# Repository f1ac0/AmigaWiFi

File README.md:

# AmigaWiFi
Three different RS232 WiFi boards with ESP8266 to connect the Amiga to the world with Zimodem or esp\_slip\_router firmwares.

With Zimodem (https://github.com/bozimmerman/Zimodem) by Bo Zimmerman, this board can connect to telnet/BBS/xyzmodem/kermit services over IP on your local network or Internet.

With esp\_slip\_router (https://github.com/martin-ger/esp\_slip\_router) by Martin Ger, this board is a SLIP router to connect your Amiga to Internet.

The boards :
- AmigaWiFi3232_external : plugs into the DB25 serial port. Provides TX/RX/RTS/CTS for communication and hardware flow control. Needs external 5V supply through micro or mini-USB.
- AmigaWiFi3232_internal : connects internally. Provides TX/RX/RTS/CTS for communication and hardware flow control.
- AmigaWifi3237 : plugs into the DB25 serial port. Provides TX/RX/RTS/CTS/DTR/DSR/DCD/RI for communication, hardware flow control, carrier detect, ring. Needs external 5V supply through micro or mini-USB. Also has LED and display header that are not implemented at the moment.

Please note that the serial port on Amiga suffers some limitations. It is dependent on CPU speed : do not expect stable transfer at more than 33600 bauds with a 7MHz 68000, even with new8n1/baudbandit serial drivers. It is also dependent on screen bitplanes so you may need to set a 4 or even 2 colours mode before transfer.

# Disclaimer
This is a hobbyist project, it comes with no warranty and no support. Also remember that the Amiga machines are about 30 years old and may fail because of such hardware expansions.

This board is not connected to the firmware authors, please don't bother them with issues you might have because of it.

I publish this work using the CC-BY-NC-SA license.

If you find it useful and want to reward me : I am always looking for Amiga/Amstrad CPC hardware to repair and hack, please contact me.

# Making it
Some components are SMD. You need to know what you are doing.

Check for shorts at least between 5V, 3.3V, and GND traces before applying power !

The programming port does not need to be soldered since it needs to be programmed just once : you can just hold it in place during the few seconds required for programming.

The ESP8266 has to be programmed with a firmware. 3232 boards need to be programmed through a RS232 serial port on your PC so you need to physically connect it to the DB9 plug (commercial or homemade adapter). 3237 board can be programmed through its RS232 DB25 or through a TTL header depending on how you build it : check the schematic. In all cases you need to connect TX of the PC to RX of the board and vice-versa.

If you use the internal version of the board, disconnect any external device from the serial port. They cannot be used at the same time.

# Using it with Zimodem
Check the Zimodem project page on how to build it with the Arduino framework.

It is required to set the pinouts before building :
```
# define DEFAULT_PIN_DSR 5  //To computer DSR
# define DEFAULT_PIN_DTR 4  //To computer DTR
# define DEFAULT_PIN_RI 2 //To computer RI
# define DEFAULT_PIN_RTS 15 //To computer CTS (warning switched)
# define DEFAULT_PIN_CTS 13 //To computer RTS (warning switched)
# define PIN_EN 12
# define PIN_SHDN 14
```

In addition for 3237 version, enable the serial converter at beginning of setup :
```
void setup()
{
#ifdef PIN_EN //Enable 3237
  pinMode(PIN_EN, OUTPUT);
  digitalWrite(PIN_EN, LOW);
#endif
#ifdef PIN_SHDN //unSHDN 3237
  pinMode(PIN_SHDN, OUTPUT);
  digitalWrite(PIN_SHDN, HIGH);
#endif
```

Setup on the Amiga :
- install some terminal software like Term_4.8
- Setup serial device with appropriate baud rate, high speed mode (8N1), appropriate flow control, NO XON/XOFF. Disable local Echo.
- Setup transfer directories, then activate zmodem auto download
- Setup Zimodem:
```
ATI
ATB38400
ATW
ATW"ssid,pwd"
AT&W
```

To connect to a telnet/bbs service :
```
ATDT"towel.blinkenlights.nl:23"
```

To transfer a file from a PC on the LAN using sz :
- On the PC : `sz -b --tcp-server Files/to/transfer Another/file/to/transfer`
- Then on the Amiga connect to your PC IP and port given by sz : `ATD"192.168.1.2:32999"`
Transfer the file to the PC :
- On the Amiga : `ATA1234`
- On the PC : `sz -b --tcp-client 192.168.1.5`

If there are too many errors and retries :
- Lower the number of colours of the terminal app or Workbench.
- Increase buffers on Amiga.
- Activate hardware flow control both on Zimodem `ATF0` and Amiga (not sure if this is meaningful though). Use `ATF4` to disable it.
- Lower bitrate both on Zimodem `ATB19200` and Amiga (not too much otherwise sz will timeout during transfer).

# Using it with esp_slip_router
Check the esp\_slip\_router page on how to build the firmware.

By default the project does not use hardware flow control. You can choose to activate it before building, which will let you use the baudbandit serial driver on the Amiga. However beware that slattach during the PC test and setup procedure will not work anymore. To enable it, make these changes in include/driver/uart.h :
```
UART_HW_RTS 1
UART_HW_CTS 1
```

To setup the Amiga side I followed the guide : https://blog.nootch.net/post/amiga-bbs-online-2019/. With few additions : enable the "ignore DSR" feature, disable "Carrier detect" and use the "New8N1" serial driver. It works on my A600 with 68020 but Genesis does not work on my A500 with 68010 (not only the license file but also starting the app).

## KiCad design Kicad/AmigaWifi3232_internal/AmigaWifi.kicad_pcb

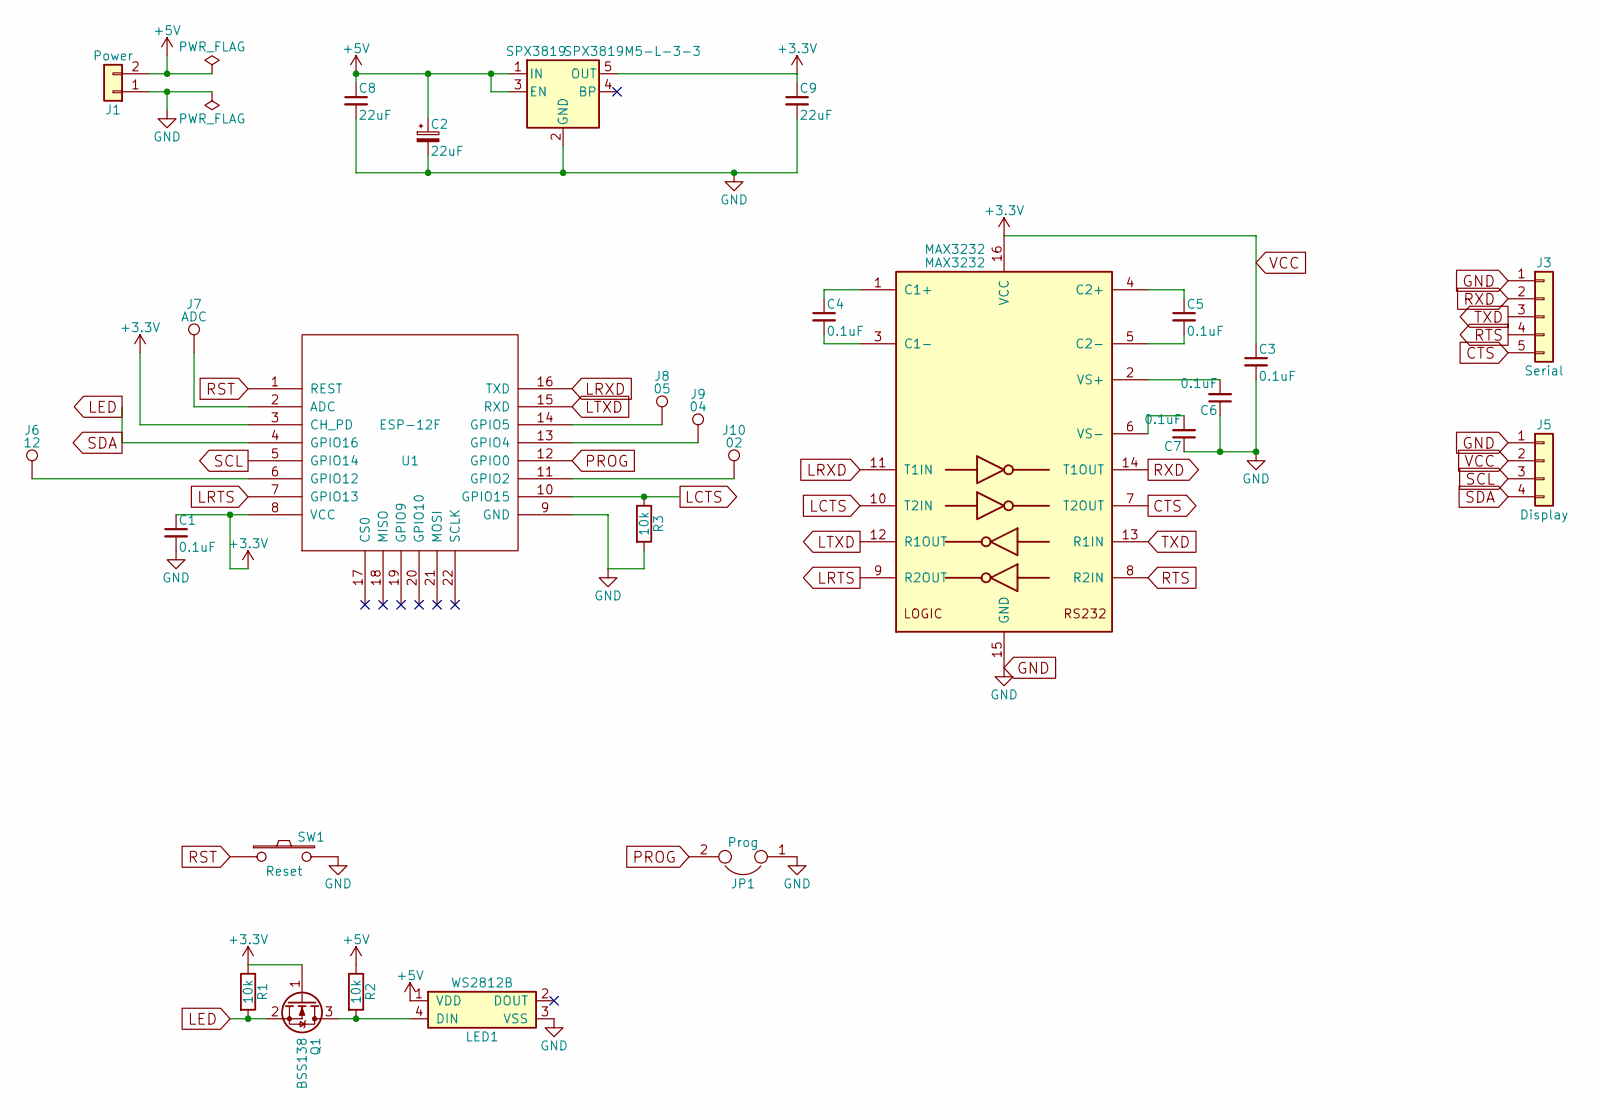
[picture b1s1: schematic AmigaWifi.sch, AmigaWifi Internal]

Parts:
C1, C3, C4, C5, C6, C7: 0.1uF; C_0805_HandSoldering
C2: 22uF; CP_Radial_D5.0mm_P2.50mm
C8, C9: 22uF; C_0805_HandSoldering
J1: Power; Pin_Header_Straight_1x02_Pitch2.54mm
J3: Serial; Pin_Header_Straight_1x05_Pitch2.54mm
J5: Display; Pin_Header_Straight_1x04_Pitch2.54mm
J6: 12; Measurement_Point_Round-SMD-Pad_Small
J7: ADC; Measurement_Point_Round-SMD-Pad_Small
J8: 05; Measurement_Point_Round-SMD-Pad_Small
J9: 04; Measurement_Point_Round-SMD-Pad_Small
J10: 02; Measurement_Point_Round-SMD-Pad_Small
JP1: Prog; Pin_Header_Straight_1x02_Pitch2.54mm
LED1: WS2812B; LED_WS2812B-PLCC4
MAX3232: MAX3232; SOIC-16_3.9x9.9mm_Pitch1.27mm
Q1: BSS138; SOT-23_Handsoldering
R1, R2, R3: 10k; R_0805_HandSoldering
SPX3819: SPX3819M5-L-3-3; SOT-23-5_HandSoldering
SW1: Reset; SW_SPST_FSMSM
U1: ESP-12F; ESP-12E_SMD

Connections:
+5V: C2.1, C8.1, J1.2, LED1.1 (VDD), R2.1, SPX3819.1 (IN), SPX3819.3 (EN)
CTS: J3.5, MAX3232.7 (T2OUT)
GND: C1.2, C2.2, C3.2, C6.1, C7.1, C8.2, C9.2, J1.1, J3.1, J5.1, JP1.1, LED1.3 (VSS), MAX3232.15 (GND), R3.2, SPX3819.2 (GND), SW1.2, U1.9 (GND)
LCTS: MAX3232.10 (T2IN), R3.1, U1.10 (GPIO15)
LED: J5.4, Q1.2 (S), R1.2, U1.4 (GPIO16)
LRTS: MAX3232.9 (R2OUT), U1.7 (GPIO13)
LRXD: MAX3232.11 (T1IN), U1.16 (TXD)
LTXD: MAX3232.12 (R1OUT), U1.15 (RXD)
unnamed: C4.1, MAX3232.1 (C1+)
unnamed: C4.2, MAX3232.3 (C1-)
unnamed: C5.1, MAX3232.4 (C2+)
unnamed: C5.2, MAX3232.5 (C2-)
unnamed: C6.2, MAX3232.2 (VS+)
unnamed: C7.2, MAX3232.6 (VS-)
unnamed: J6.1, U1.6 (GPIO12)
unnamed: J7.1, U1.2 (ADC)
unnamed: J8.1, U1.14 (GPIO5)
unnamed: J9.1, U1.13 (GPIO4)
unnamed: J10.1, U1.11 (GPIO2)
unnamed: LED1.4 (DIN), Q1.3 (D), R2.2
PROG: JP1.2, U1.12 (GPIO0)
RST: SW1.1, U1.1 (REST)
RTS: J3.4, MAX3232.8 (R2IN)
RXD: J3.2, MAX3232.14 (T1OUT)
SCL: J5.3, U1.5 (GPIO14)
TXD: J3.3, MAX3232.13 (R1IN)
VCC: C1.1, C3.1, C9.1, J5.2, MAX3232.16 (VCC), Q1.1 (G), R1.1, SPX3819.5 (OUT), U1.3 (CH_PD), U1.8 (VCC)

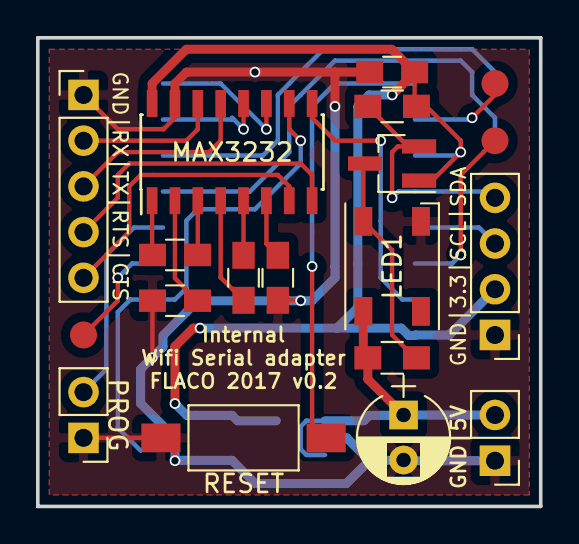
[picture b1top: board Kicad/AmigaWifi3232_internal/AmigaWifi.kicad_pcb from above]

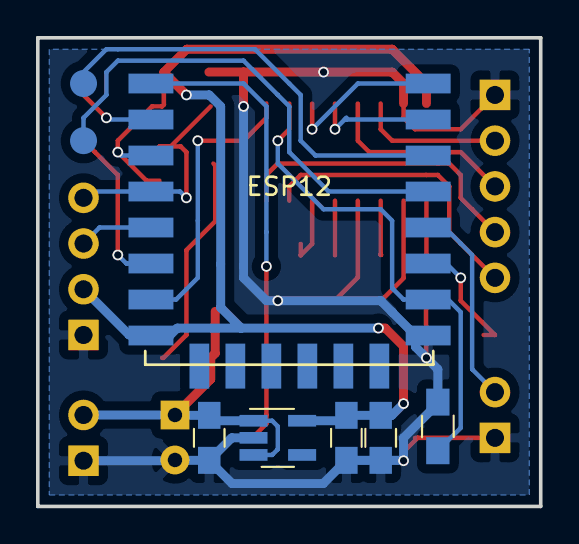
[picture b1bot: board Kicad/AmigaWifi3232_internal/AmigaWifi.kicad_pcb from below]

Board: 2 copper layers, 27.9 x 26.0 mm, 27 parts (8 on the bottom side), 27 nets.

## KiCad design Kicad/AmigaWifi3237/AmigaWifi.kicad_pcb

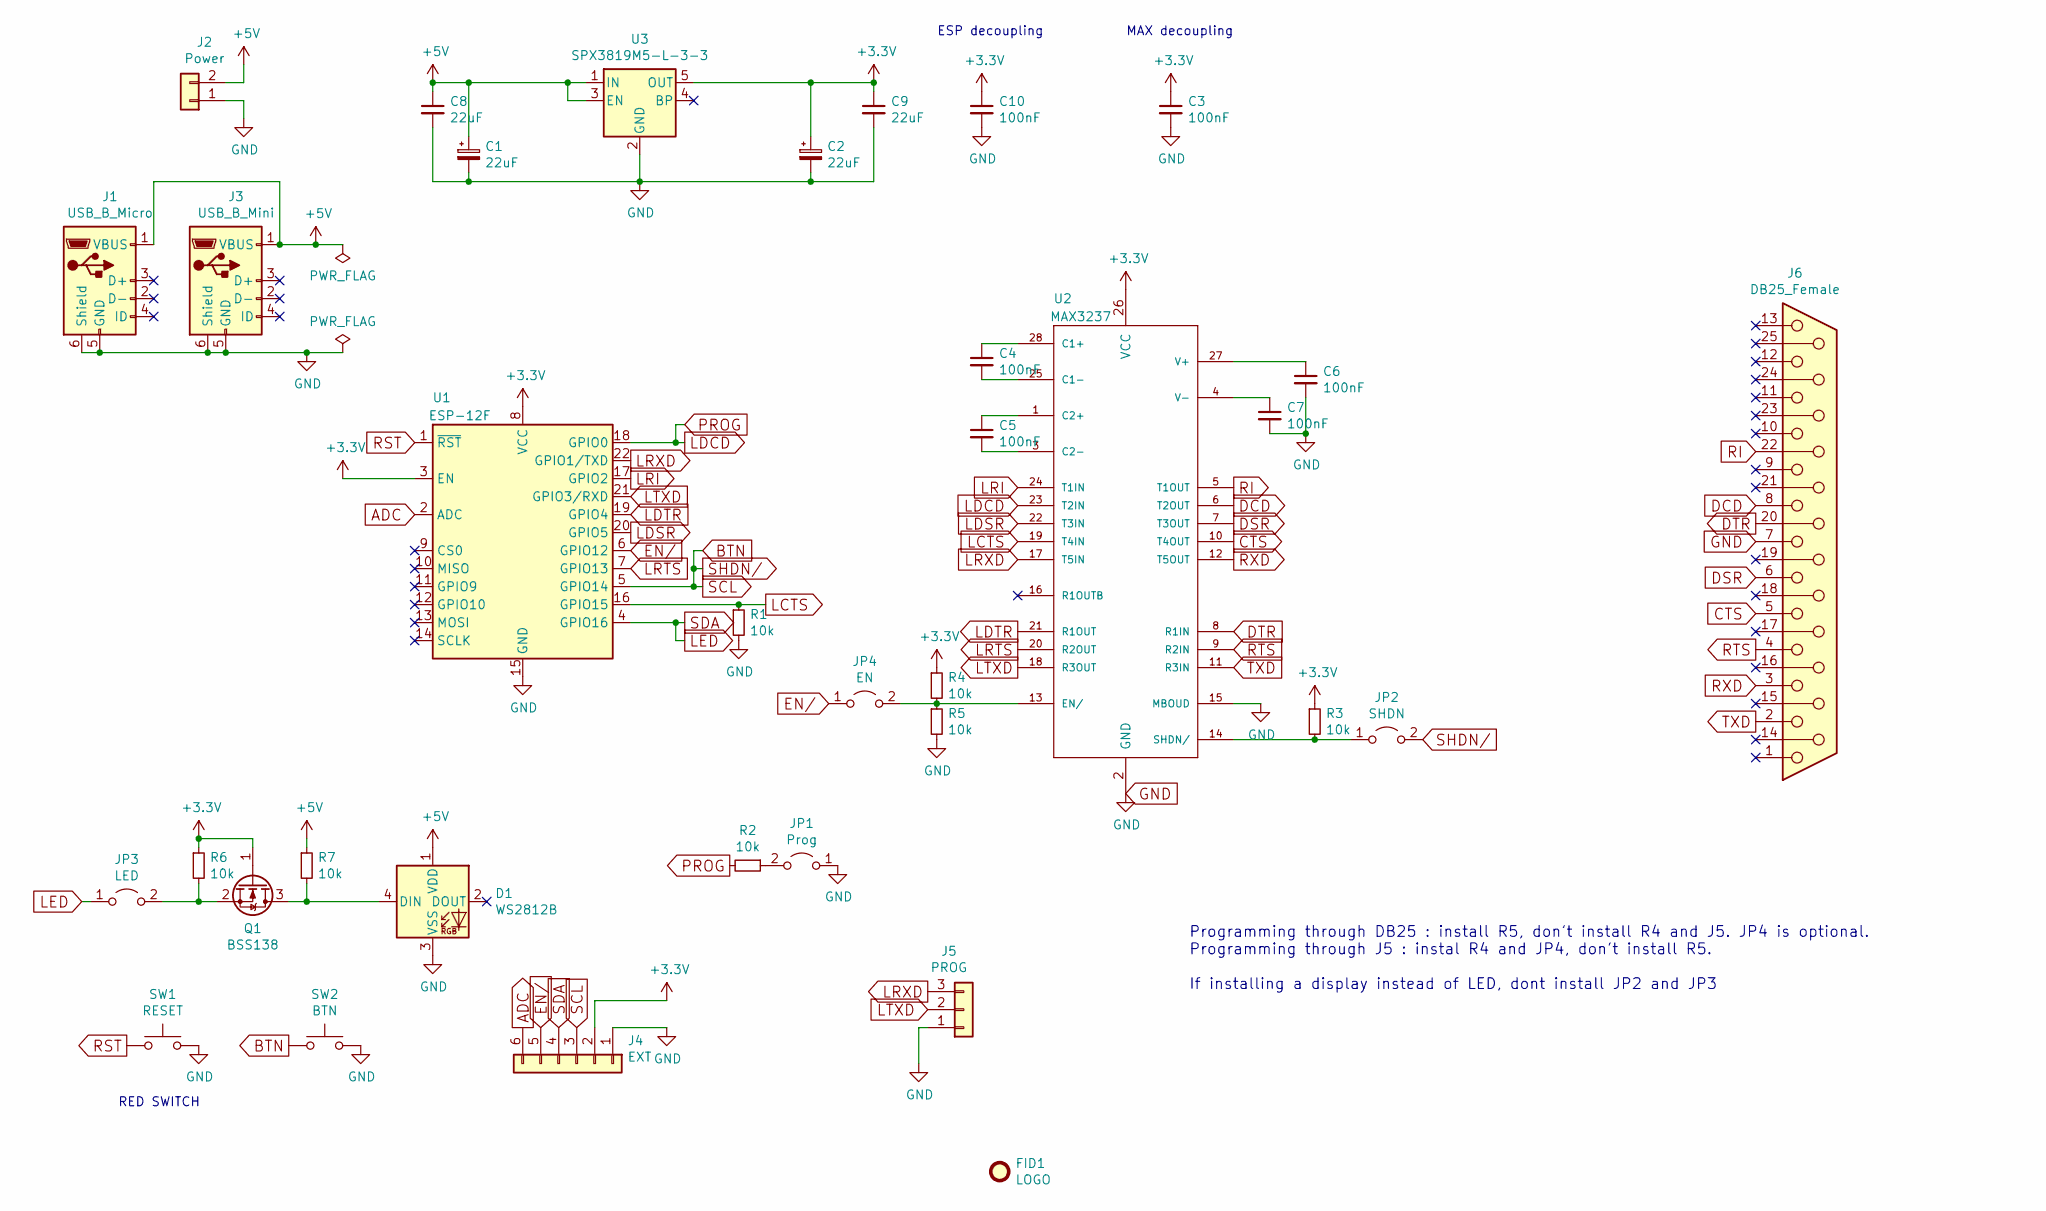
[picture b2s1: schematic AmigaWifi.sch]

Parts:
C1, C2: 22uF; CP_Radial_D5.0mm_P2.50mm
C3, C4, C5, C6, C7, C10: 100nF; C_0805_2012Metric_Pad1.15x1.40mm_HandSolder
C8, C9: 22uF; C_0805_2012Metric_Pad1.15x1.40mm_HandSolder
D1: WS2812B; LED_WS2812B_PLCC4_5.0x5.0mm_P3.2mm
FID1: LOGO; CC_BY_NC_SA_square_copper
J1: USB_B_Micro; USB_Micro-B_Molex-105017-0001
J2: Power; PinHeader_1x02_P2.54mm_Vertical
J3: USB_B_Mini; USB_Mini-B_Lumberg_2486_01_Horizontal
J4: EXT; PinHeader_1x06_P2.54mm_Vertical
J5: PROG; PinHeader_1x03_P2.54mm_Vertical
J6: DB25_Female; DSUB-25_Female_EdgeMount_P2.77mm
JP1: Prog; PinHeader_1x02_P2.54mm_Vertical
JP2: SHDN; SolderJumper-2_P1.3mm_Open_RoundedPad1.0x1.5mm
JP3: LED; SolderJumper-2_P1.3mm_Open_RoundedPad1.0x1.5mm
JP4: EN; SolderJumper-2_P1.3mm_Open_RoundedPad1.0x1.5mm
Q1: BSS138; SOT-23_Handsoldering
R1, R2, R3, R4, R5, R6, R7: 10k; R_0805_2012Metric_Pad1.15x1.40mm_HandSolder
SW1: RESET; SW_SPST_FSMSM
SW2: BTN; SW_SPST_FSMSM
U1: ESP-12F; ESP-12E
U2: MAX3237; SSOP-28_5.3x10.2mm_P0.65mm
U3: SPX3819M5-L-3-3; SOT-23-5_HandSoldering

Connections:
+3V3: C2.1, C3.1, C9.1, C10.1, J4.2, Q1.1 (G), R3.1, R4.1, R6.1, U1.3 (EN), U1.8 (VCC), U2.26 (VCC), U3.5 (OUT)
+5V: C1.1, C8.1, D1.1 (VDD), J1.1 (VBUS), J2.2, J3.1 (VBUS), R7.1, U3.1 (IN), U3.3 (EN)
ADC: J4.6, U1.2 (ADC)
BTN: J4.3, JP2.2 (B), SW2.1, U1.5 (GPIO14)
CTS: J6.5, U2.10 (T4OUT)
DCD: J6.8, U2.6 (T2OUT)
DSR: J6.6, U2.7 (T3OUT)
DTR: J6.20, U2.8 (R1IN)
EN/: J4.5, JP4.1 (A), U1.6 (GPIO12)
GND: C1.2, C2.2, C3.2, C6.2, C7.2, C8.2, C9.2, C10.2, D1.3 (VSS), J1.5 (GND), J1.6 (Shield), J2.1, J3.5 (GND), J3.6 (Shield), J4.1, J5.1, J6.7, JP1.1 (A), R1.2, R5.2, SW1.2, SW2.2, U1.15 (GND), U2.2 (GND), U2.15 (MBOUD), U3.2 (GND)
LCTS: R1.1, U1.16 (GPIO15), U2.19 (T4IN)
LDCD: R2.2, U1.18 (GPIO0), U2.23 (T2IN)
LDSR: U1.20 (GPIO5), U2.22 (T3IN)
LDTR: U1.19 (GPIO4), U2.21 (R1OUT)
LED: J4.4, JP3.1 (A), U1.4 (GPIO16)
LRI: U1.17 (GPIO2), U2.24 (T1IN)
LRTS: U1.7 (GPIO13), U2.20 (R2OUT)
LRXD: J5.3, U1.22 (GPIO1/TXD), U2.17 (T5IN)
LTXD: J5.2, U1.21 (GPIO3/RXD), U2.18 (R3OUT)
unnamed: C4.1, U2.28 (C1+)
unnamed: C4.2, U2.25 (C1-)
unnamed: C5.1, U2.1 (C2+)
unnamed: C5.2, U2.3 (C2-)
unnamed: C6.1, U2.27 (V+)
unnamed: C7.1, U2.4 (V-)
unnamed: D1.4 (DIN), Q1.3 (D), R7.2
unnamed: JP1.2 (B), R2.1
unnamed: JP2.1 (A), R3.2, U2.14 (SHDN/)
unnamed: JP3.2 (B), Q1.2 (S), R6.2
unnamed: JP4.2 (B), R4.2, R5.1, U2.13 (EN/)
RI: J6.22, U2.5 (T1OUT)
RST: SW1.1, U1.1 (~RST)
RTS: J6.4, U2.9 (R2IN)
RXD: J6.3, U2.12 (T5OUT)
TXD: J6.2, U2.11 (R3IN)

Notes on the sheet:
Programming through DB25 : install R5, don't install R4 and J5. JP4 is optional. Programming through J5 : instal R4 and JP4, don't install R5. If installing a display instead of LED, dont install JP2 and JP3
ESP decoupling
RED SWITCH
MAX decoupling

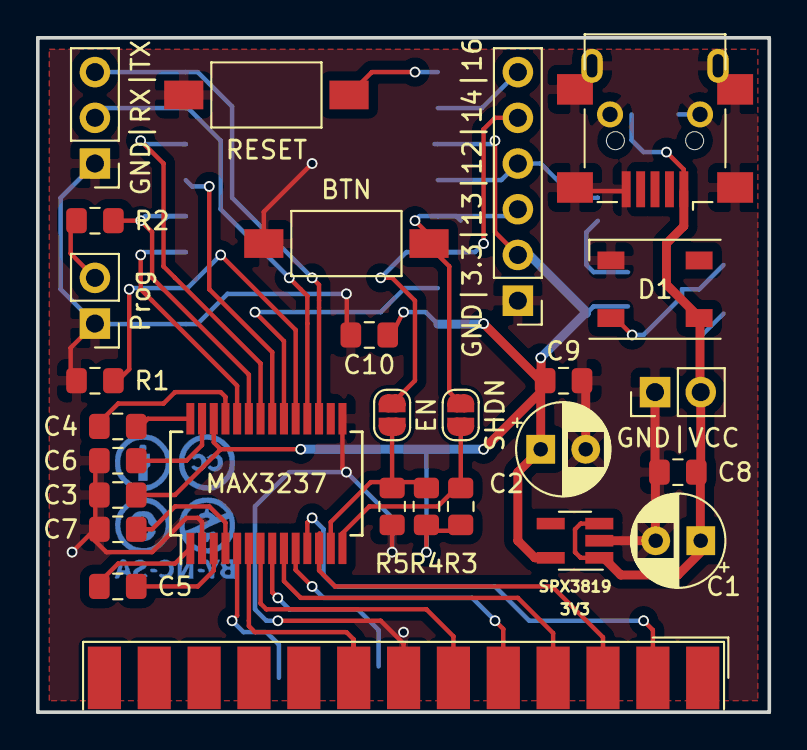
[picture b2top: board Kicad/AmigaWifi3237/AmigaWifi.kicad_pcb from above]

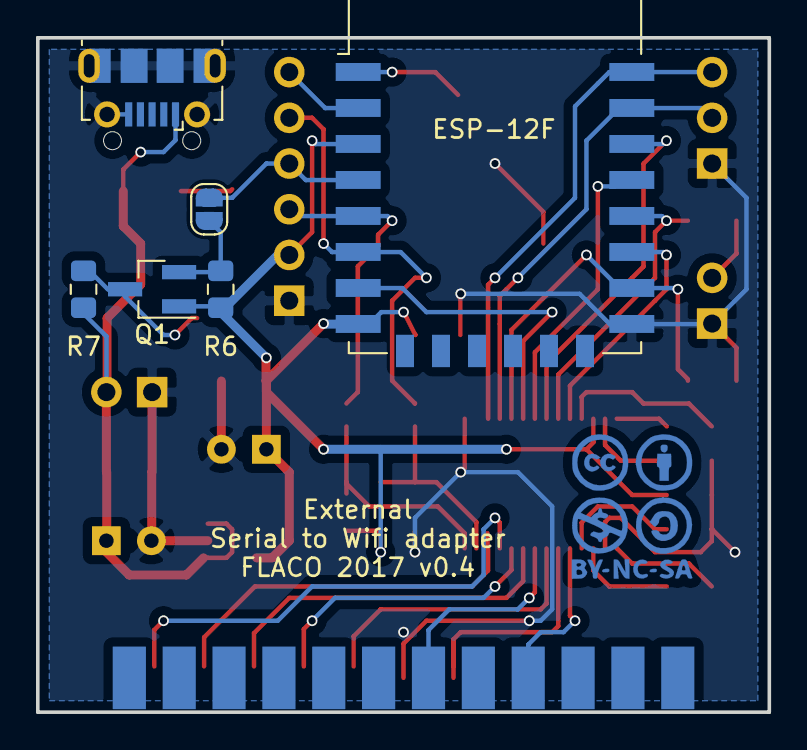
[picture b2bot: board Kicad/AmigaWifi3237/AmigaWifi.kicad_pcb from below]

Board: 2 copper layers, 40.6 x 37.5 mm, 35 parts (7 on the bottom side), 35 nets.

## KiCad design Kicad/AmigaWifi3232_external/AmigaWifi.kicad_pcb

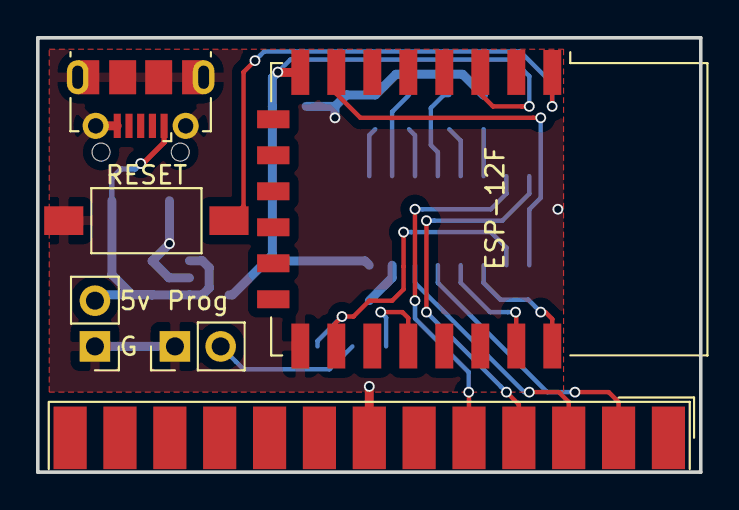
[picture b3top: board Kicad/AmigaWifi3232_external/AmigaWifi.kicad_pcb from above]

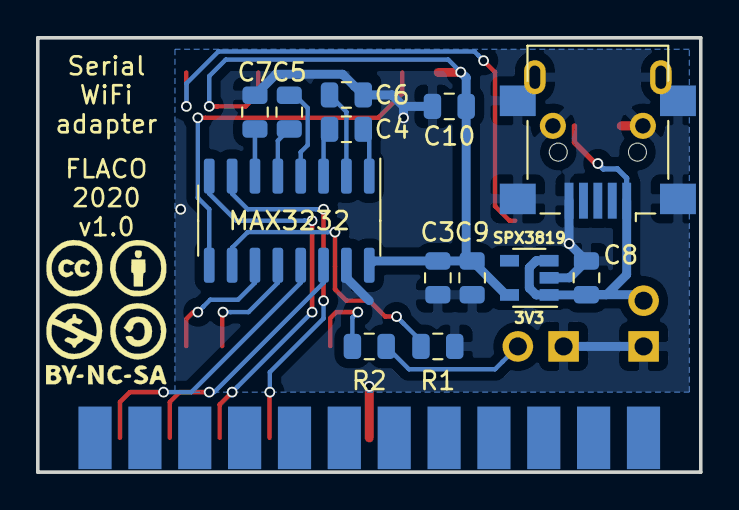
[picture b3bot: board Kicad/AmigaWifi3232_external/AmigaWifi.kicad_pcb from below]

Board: 2 copper layers, 36.8 x 24.1 mm, 20 parts (14 on the bottom side), 20 nets.

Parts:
C3, C4, C5, C6, C7, C10: 100nF; C_0805_2012Metric
C8, C9: 22uF; C_0805_2012Metric
FID1: LOGO; CC_BY_NC_SA_square_silkscreen
J1: USB_B_Micro; USB_Micro-B_Molex-105017-0001
J2: Power; PinHeader_1x02_P2.54mm_Vertical
J3: USB_B_Mini; USB_Mini-B_Lumberg_2486_01_Horizontal
J6: DB25_Female; DSUB-25_Female_EdgeMount_P2.77mm
JP1: Prog; PinHeader_1x02_P2.54mm_Vertical
R1, R2: 10k; R_0805_2012Metric
SW1: RESET; SW_SPST_FSMSM
U1: ESP-12F; ESP-12E
U2: MAX3232; SOIC-16_3.9x9.9mm_P1.27mm
U3: SPX3819M5-L-3-3; SOT-23-5

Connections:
+3V3: C3.1, C9.1, C10.1, U1.3, U1.8, U2.16, U3.5
+5V: C8.1, J1.1, J2.2, J3.1, U3.1, U3.3
CTS: J6.5, U2.7
GND: C3.2, C6.1, C7.1, C8.2, C9.2, C10.2, J1.5, J1.6, J2.1, J3.5, J3.6, J6.7, JP1.1, R1.2, SW1.2, U1.15, U2.15, U3.2
LCTS: R1.1, U1.16, U2.10
LRTS: U1.7, U2.9
LRXD: U1.22, U2.11
LTXD: U1.21, U2.12
unnamed: C4.1, U2.1
unnamed: C4.2, U2.3
unnamed: C5.1, U2.4
unnamed: C5.2, U2.5
unnamed: C6.2, U2.2
unnamed: C7.2, U2.6
unnamed: JP1.2, R2.1
PROG: R2.2, U1.18
RST: SW1.1, U1.1
RTS: J6.4, U2.8
RXD: J6.3, U2.14
TXD: J6.2, U2.13

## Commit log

2020-09-07 Respository init with KiCAD files, Readme and License
2022-02-17 Photo, and README

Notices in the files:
Kicad/AmigaWifi3232_external/AmigaWifi.kicad_pcb:
FLACO 2018-2020, licence of this PCB is CC-BY-NC-SA
Kicad/AmigaWifi3232_external/AmigaWifi.sch:
FLACO 2018, licence of this schematic is CC-BY-NC-SA
Kicad/AmigaWifi3232_internal/AmigaWifi.kicad_pcb:
FLACO 2019, licence of this PCB is CC-BY-NC-SA
Kicad/AmigaWifi3237/AmigaWifi.kicad_pcb:
FLACO 2018, licence of this PCB is CC-BY-NC-SA
